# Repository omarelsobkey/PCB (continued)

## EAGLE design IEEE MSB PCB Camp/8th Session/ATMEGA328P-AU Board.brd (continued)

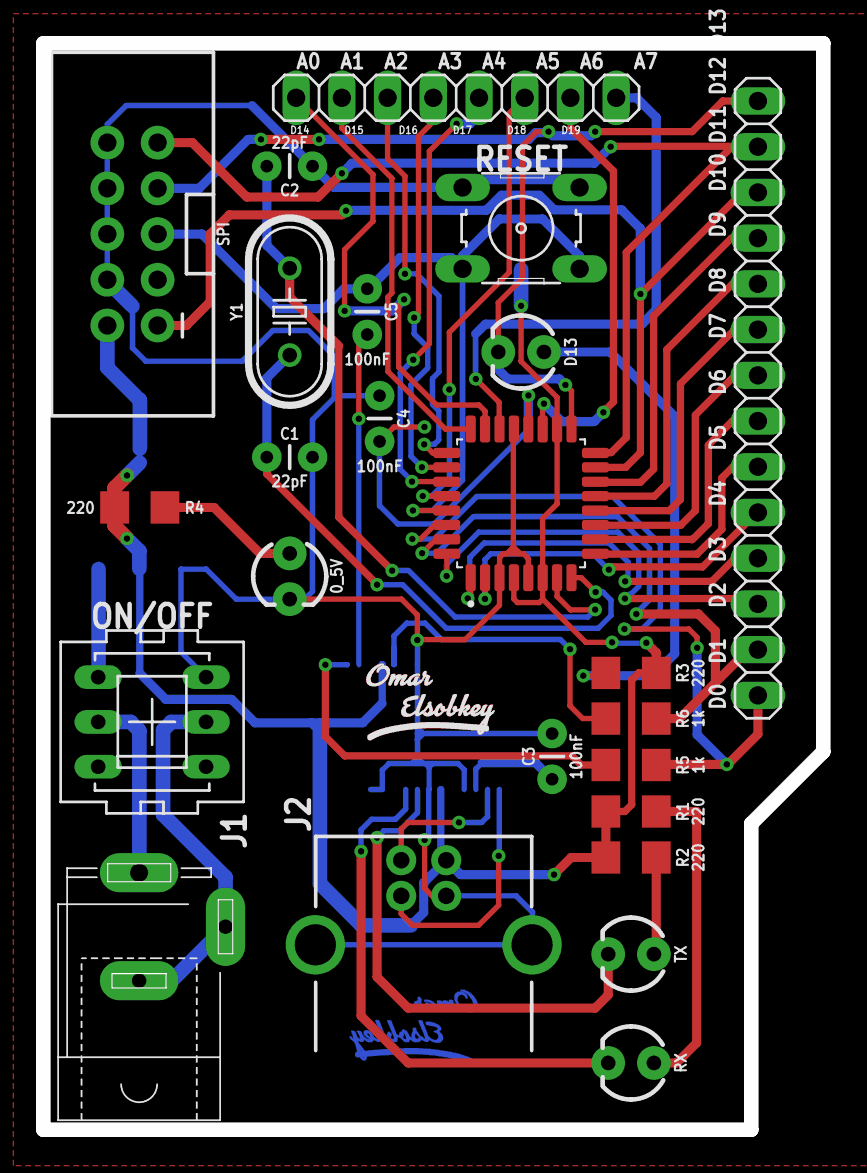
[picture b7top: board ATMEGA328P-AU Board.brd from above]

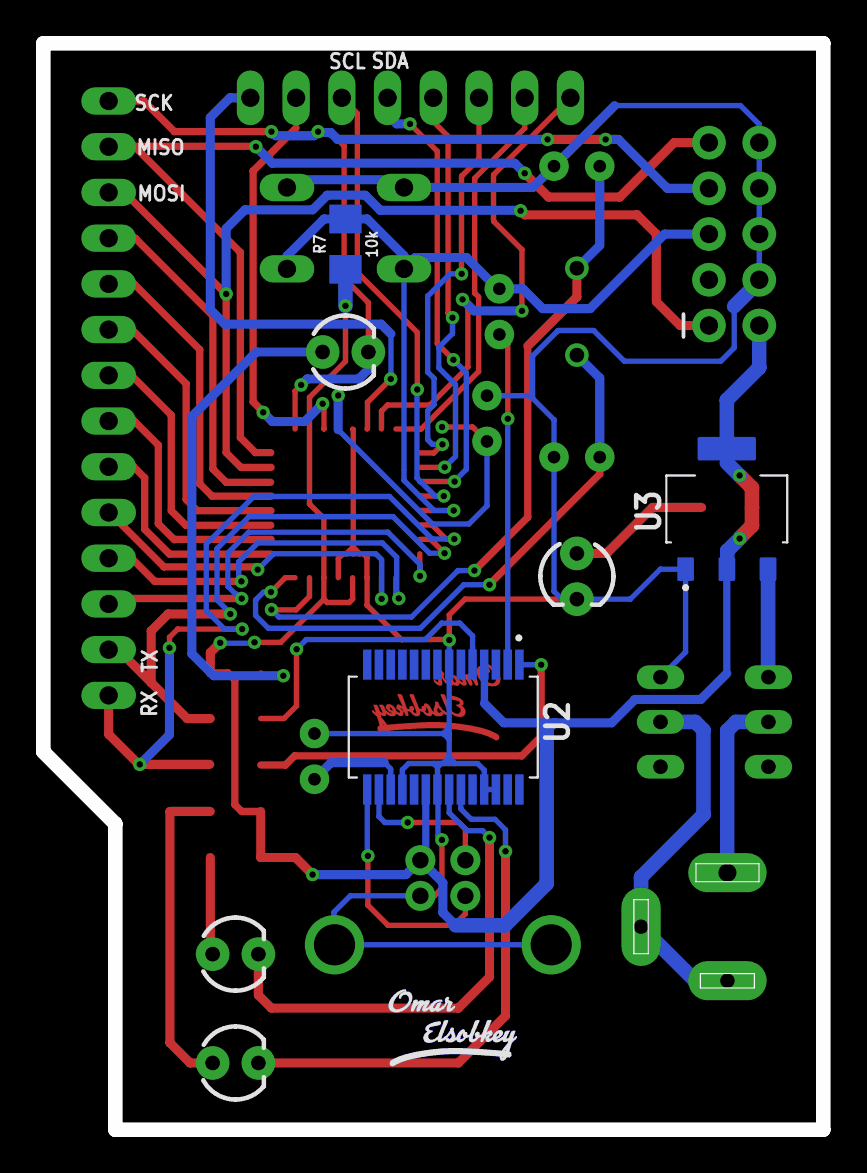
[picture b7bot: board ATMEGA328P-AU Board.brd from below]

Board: 2 copper layers, 43.3 x 60.4 mm, 29 parts (4 on the bottom side), 43 nets.

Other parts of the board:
U$1, U$2: OMAR_ELSOBKEY_X0.5
